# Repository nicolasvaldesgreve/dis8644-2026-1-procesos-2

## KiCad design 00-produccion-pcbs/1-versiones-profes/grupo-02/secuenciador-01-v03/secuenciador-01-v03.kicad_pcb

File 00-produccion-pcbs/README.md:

# produccion-pcbs

jornada maratónica sábado 06 junio 2026

equipo docente toma todos los proyectos de kicad entregados el día anterior, de proyecto-02, y con eso edita, revisa, y envía a producción.

hay 6 grupos de trabajo con una temática en particular, cada grupo realizó 2 esquemáticos con sus respectivas placas, en varias versiones que subieron a la carpeta 00-proyecto-02.

a continuación los apuntes de las distintas revisiones hechas de estos proyectos, para prepararlos para su producción física.

en este repo creamos 3 carpetas:

- 0-versiones-estudiantes: archivos de kicad con las versiones más recientes de proyectos de estudiantes
- 1-versiones-profes: archivos de kicad con las versiones revisadas y realizadas por equipo docentes
- 2-archivos-produccion: gerbers de producción, etiquetados como revA.

## grupo-01: piezos

- benjaminalvarez21
- Anaysval
- chknngttts
- ryukivol
- nicolasvaldesgreve

### g-01-pie-01-rev-a

- cambiamos tamaño r15
- cambiamos conector de entrada
- cambiamos nomenclatura de "100 u" a "100u"
- cambiamos huella de transistor Q1, porque era la equivocada

### g-01-pie-02-rev-a

- no fue enviado a producción porque no tenemos garantía de que funcionara según lo visto en protoboard.

## grupo-02: secuenciadores

- isidoraalvarez
- tomascatri
- dayanapanitrur
- Estrabismx
- angel-udp

### g-02-sec-01-rev-a

en esquemático:

- agregamos resistor de clock in a ground, para pulldown.
- agregamos resistor entre 4040 Q0 patita 9 y salida
- agregamos resistor a cada salida de jack switch.
- cambiamos huellas de transistores a versión inline_wide para que tengan más espacio
- agregados mounting hole faltantes

en pcb:

- actualizamos conectores jack a la huella de la biblioteca, para poder rutear bien los nuevos resistores y no perdernos.

### g-02-sec-02-rev-a

en esquemático:

- agregamos también resistores de protección en entradas y salidas.
- agregados mounting hole faltantes

en pcb:

- actualizamos conectores jack a la huella de la biblioteca, para poder rutear bien los nuevos resistores y no perdernos.

## grupo-03: osciladores 1

- vanessagarciaM
- antoloch
- ccarlabelenn
- arielorozco024
- Narelyriquelme

### g-03-osc-01-rev-a

- C1 estaba rotado, fue corregido.
- audio jack de entrada y salida estaban mal conectados
- condensador de salida fue cambiado por uno no polarizado

### g-03-osc-02-rev-a

- renombrar C3 a 4u7
- cambiado C1 por condensador polarizado
- 40106 fue usado como dos chips distintos, en vez de usar varios schmitt triggers desde un mismo chip, tuvimos que hacer esos cambios
- volvimos a rutear casi todo, ya que se bajó de 2 chips a 1

## grupo-04: osciladores 2

- antokiaraa
- santiagocifuvelez
- paulafuentesm
- kristelagj
- catalinaoyanedel
- yairaruiz

### g-04-osc-01-rev-a

- borramos amplificador para que esté en otro módulo
- agregamos resistencia de salida
- conectamos bien el jack de salida de audio que tenía problemas

### g-04-osc-02-rev-a

- borramos amplificador para que esté en otro módulo
- agregamos valor a diodo faltante
- corregimos símbolo de los potenciómetros
- agregamos resistencia de salida
- agregamos jack de salida de audio

## grupo-05: filtros

- antoniaamc
- Catabalboa
- sebastianguevaralarotta
- CatalinaJeria
- Luisaatoro9

### g-05-fil-01-rev-a

- error grave en la nomenclatura de los proyectos: el 01 en su README dicen que es el activo, pero en Kicad es el pasivo
- cambiamos C1 por condensador no polarizado
- conectamos patita del medio de potenciómetro
- confusión en los tamaños de los condensadores C4 y C5
- los tamaños de las pistas usados no fueron los indicados en clases ni en estandarización
- faltó el paso de agregar tierra a la placa, no está hecho

### g-05-fil-02-rev-a

- error grave en la nomenclatura de los proyectos: el 01 en su README dicen que es el activo, pero en Kicad es el pasivo
- no fue enviado a producción, ya que no funcionó en protoboard

## grupo-06: percusiones

- terroiblea
- martinaechavarria-stack
- Nicolas-Miranda1312
- paredesvania
- Coff4

### g-06-perc-01-rev-a

- agregamos jack de entrada de audio que reemplace la oscilación de entrada
- agregamos ground a los integrados que no están siendo usados

### g-06-perc-02-rev-a

- agregamos el detalle de las entradas de las compuertas lógicas no usadas, fueron conectadas a tierra, para definir sus estados
- C7 estaba en el esquemático pero no en la placa, tuvimos que agregarlo
- C4 le faltaba una conexión en la PCB, la agregamos

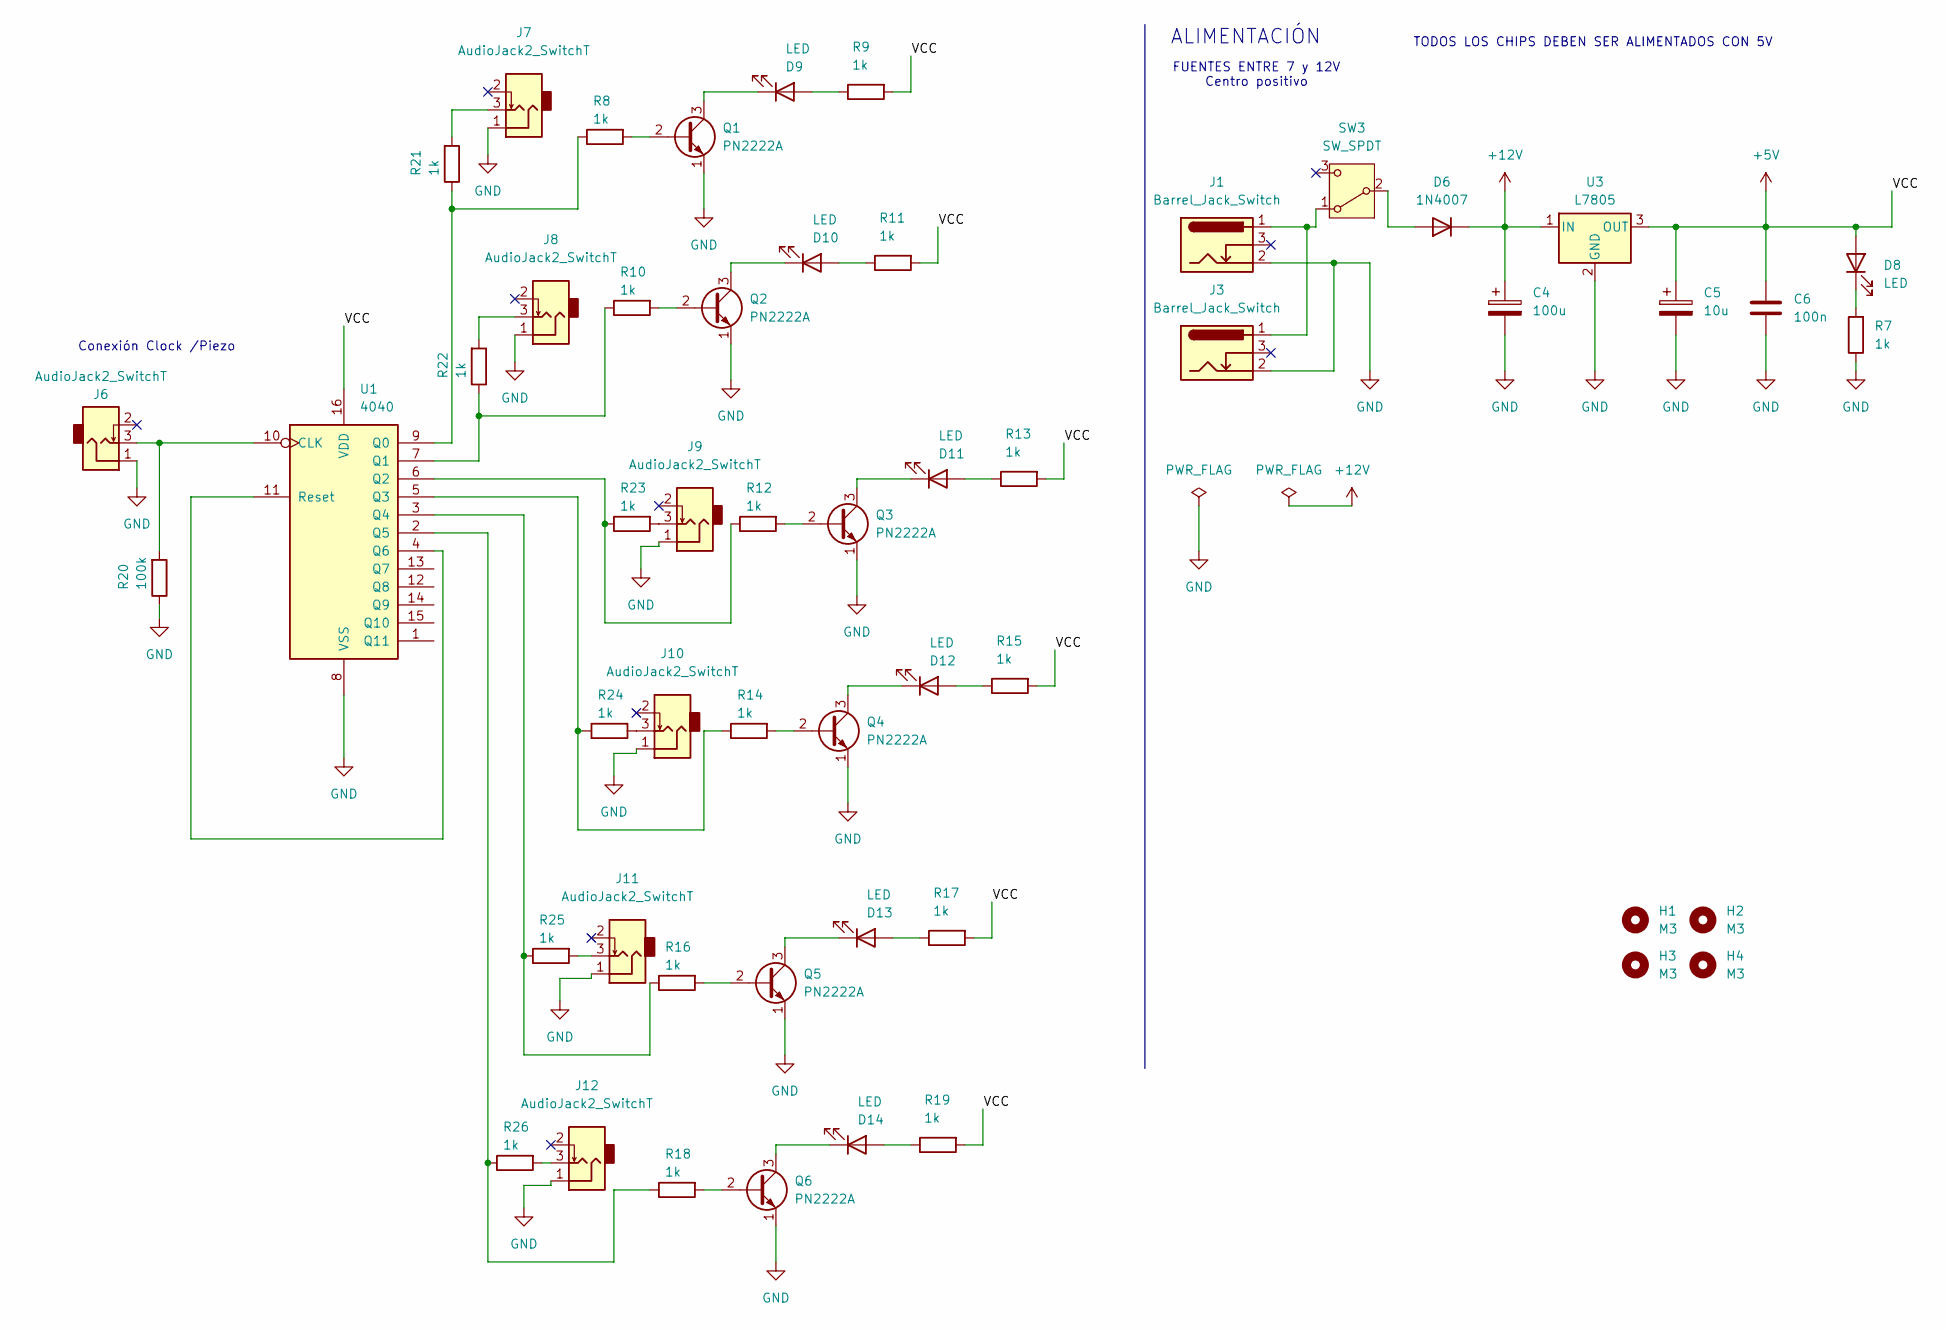
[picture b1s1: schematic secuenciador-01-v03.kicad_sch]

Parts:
C4: 100u; CP_Radial_D8.0mm_P3.80mm
C5: 10u; CP_Radial_D4.0mm_P2.00mm
C6: 100n; C_Disc_D5.0mm_W2.5mm_P2.50mm
D6: 1N4007; D_DO-41_SOD81_P10.16mm_Horizontal
D8, D9, D10, D11, D12, D13, D14: LED; LED_D5.0mm
H1, H2, H3, H4: M3; MountingHole_3.2mm_M3
J1, J3: Barrel_Jack_Switch; BarrelJack_Horizontal
J6, J7, J8, J9, J10, J11, J12: AudioJack2_SwitchT; PJ301M-12
Q1, Q2, Q3, Q4, Q5, Q6: PN2222A; TO-92_Inline_Wide
R7, R8, R9, R10, R11, R12, R13, R14, R15, R16, R17, R18, R19, R21, R22, R23, R24, R25, R26: 1k; R_Axial_DIN0207_L6.3mm_D2.5mm_P10.16mm_Horizontal
R20: 100k; R_Axial_DIN0207_L6.3mm_D2.5mm_P10.16mm_Horizontal
SW3: SW_SPDT; spdt_ssd12d00g3
U1: 4040; DIP-16_W7.62mm
U3: L7805; TO-220-3_Horizontal_TabDown

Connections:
+5V: C5.1, C6.1, D8.2 (A), R9.2, R11.2, R13.2, R15.2, R17.2, R19.2, U1.16 (VDD), U3.3 (OUT)
+12V: C4.1, D6.1 (K), U3.1 (IN)
GND: C4.2, C5.2, C6.2, J1.2, J3.2, J6.1, J7.1, J8.1, J9.1, J10.1, J11.1, J12.1, Q1.1 (E), Q2.1 (E), Q3.1 (E), Q4.1 (E), Q5.1 (E), Q6.1 (E), R7.1, R20.1, U1.8 (VSS), U3.2 (GND)
unnamed: D6.2 (A), SW3.2 (B)
unnamed: D8.1 (K), R7.2
unnamed: D9.2 (A), R9.1
unnamed: D9.1 (K), Q1.3 (C)
unnamed: D10.2 (A), R11.1
unnamed: D10.1 (K), Q2.3 (C)
unnamed: D11.2 (A), R13.1
unnamed: D11.1 (K), Q3.3 (C)
unnamed: D12.2 (A), R15.1
unnamed: D12.1 (K), Q4.3 (C)
unnamed: D13.2 (A), R17.1
unnamed: D13.1 (K), Q5.3 (C)
unnamed: D14.2 (A), R19.1
unnamed: D14.1 (K), Q6.3 (C)
unnamed: J7.3, R21.2
unnamed: J8.3, R22.2
unnamed: J9.3, R23.2
unnamed: J10.3, R24.2
unnamed: J11.3, R25.2
unnamed: J12.3, R26.2
unnamed: Q1.2 (B), R8.2
unnamed: Q2.2 (B), R10.2
unnamed: Q3.2 (B), R12.2
unnamed: Q4.2 (B), R14.2
unnamed: Q5.2 (B), R16.2
unnamed: Q6.2 (B), R18.2
unnamed: J1.1, J3.1, SW3.1 (A)
unnamed: J6.3, R20.2, U1.10 (CLK)
unnamed: R8.1, R21.1, U1.9 (Q0)
unnamed: R10.1, R22.1, U1.7 (Q1)
unnamed: R12.1, R23.1, U1.6 (Q2)
unnamed: R14.1, R24.1, U1.5 (Q3)
unnamed: R16.1, R25.1, U1.3 (Q4)
unnamed: R18.1, R26.1, U1.2 (Q5)
unnamed: U1.4 (Q6), U1.11 (Reset)

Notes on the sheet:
Conexión Clock /Piezo
ALIMENTACIÓN
FUENTES ENTRE 7 y 12V Centro positivo
TODOS LOS CHIPS DEBEN SER ALIMENTADOS CON 5V

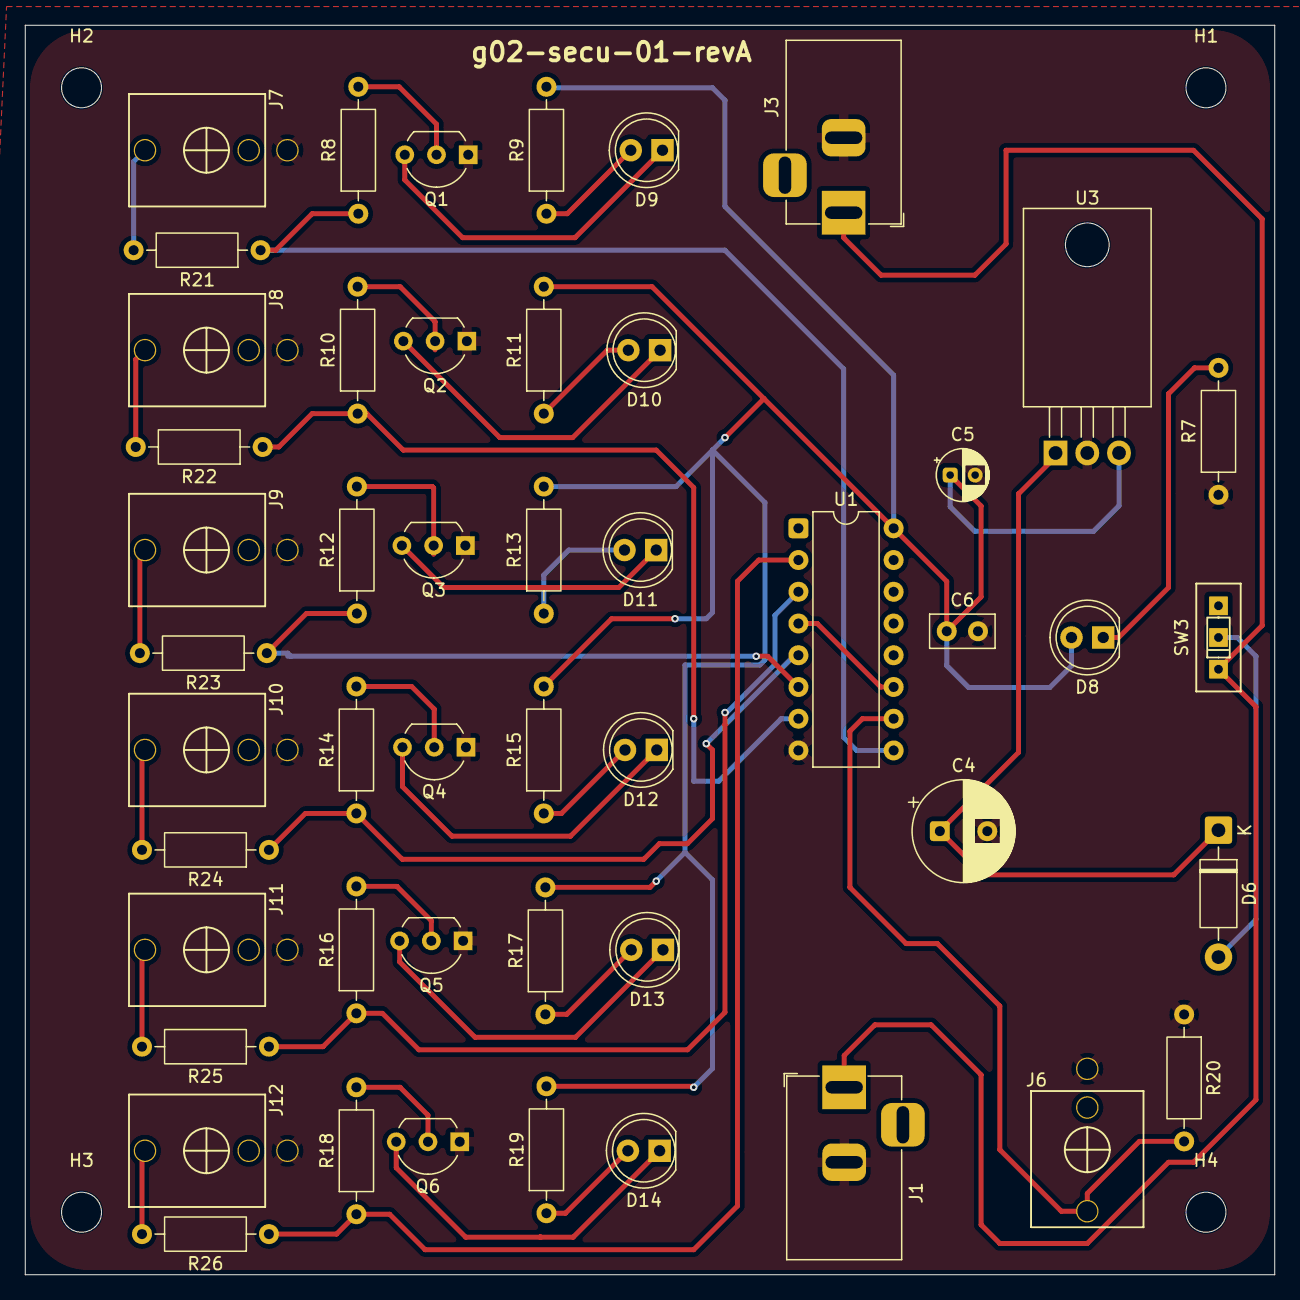
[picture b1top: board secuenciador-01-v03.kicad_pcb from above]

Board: 2 copper layers, 100.0 x 100.0 mm, 53 parts (0 on the bottom side), 38 nets.

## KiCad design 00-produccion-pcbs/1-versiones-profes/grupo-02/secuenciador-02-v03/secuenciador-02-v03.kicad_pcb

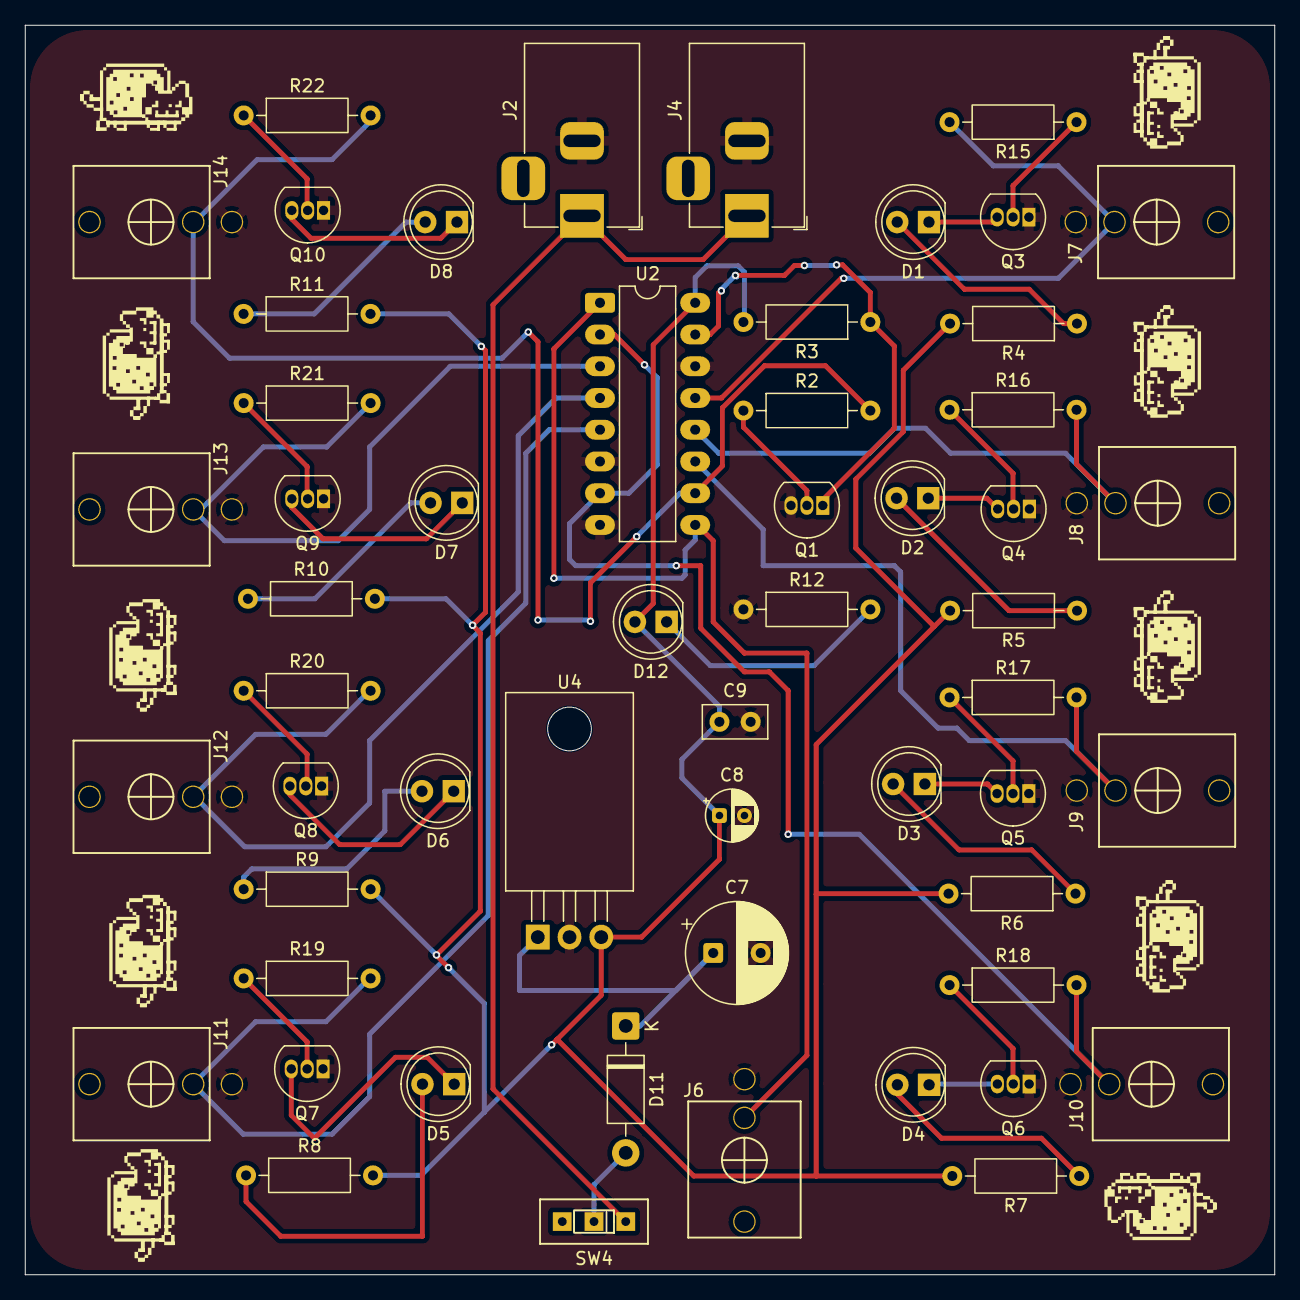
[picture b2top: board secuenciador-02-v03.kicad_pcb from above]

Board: 2 copper layers, 100.0 x 100.0 mm, 55 parts (0 on the bottom side), 41 nets.

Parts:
C7: 100u; CP_Radial_D8.0mm_P3.80mm
C8: 10u; CP_Radial_D4.0mm_P2.00mm
C9: 100n; C_Disc_D5.0mm_W2.5mm_P2.50mm
D1, D2, D3, D4, D5, D6, D7, D8, D12: LED; LED_D5.0mm
D11: 1N4007; D_DO-41_SOD81_P10.16mm_Horizontal
J2, J4: Barrel_Jack_Switch; BarrelJack_Horizontal
J6, J7, J8, J9, J10, J11, J12, J13, J14: AudioJack2_SwitchT; PJ301M-12
Q1: BC548; TO-92_Inline
Q3, Q4, Q5, Q6, Q7, Q8, Q9, Q10: PN2222A; TO-92_Inline
R2: 10k; R_Axial_DIN0207_L6.3mm_D2.5mm_P10.16mm_Horizontal
R3, R12, R15, R16, R17, R18, R19, R20, R21, R22: 1k; R_Axial_DIN0207_L6.3mm_D2.5mm_P10.16mm_Horizontal
R4, R5, R6, R7, R8, R9, R10, R11: 220; R_Axial_DIN0207_L6.3mm_D2.5mm_P10.16mm_Horizontal
SW4: SW_SPDT; spdt_ssd12d00g3
U2: 4015; DIP-16_W7.62mm_LongPads
U4: L7805; TO-220-3_Horizontal_TabDown

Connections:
+5V: C8.1, C9.1, D12.2 (A), R3.2, R4.2, R5.2, R6.2, R7.2, R8.2, R9.2, R10.2, R11.2, U2.16 (Vdd), U4.3 (OUT)
+12V: C7.1, D11.1 (K), U4.1 (IN)
GND: C7.2, C8.2, C9.2, J2.2, J4.2, J6.1, J7.1, J8.1, J9.1, J10.1, J11.1, J12.1, J13.1, J14.1, Q1.3 (E), Q3.1 (E), Q4.1 (E), Q5.1 (E), Q6.1 (E), Q7.1 (E), Q8.1 (E), Q9.1 (E), Q10.1 (E), R12.1, U2.6 (MR), U2.8 (Vss), U2.14 (MR), U4.2 (GND)
unnamed: D1.2 (A), R4.1
unnamed: D1.1 (K), Q3.3 (C)
unnamed: D2.2 (A), R5.1
unnamed: D2.1 (K), Q4.3 (C)
unnamed: D3.2 (A), R6.1
unnamed: D3.1 (K), Q5.3 (C)
unnamed: D4.2 (A), R7.1
unnamed: D4.1 (K), Q6.3 (C)
unnamed: D5.2 (A), R8.1
unnamed: D5.1 (K), Q7.3 (C)
unnamed: D6.2 (A), R9.1
unnamed: D6.1 (K), Q8.3 (C)
unnamed: D7.2 (A), R10.1
unnamed: D7.1 (K), Q9.3 (C)
unnamed: D8.2 (A), R11.1
unnamed: D8.1 (K), Q10.3 (C)
unnamed: D11.2 (A), SW4.2 (B)
unnamed: D12.1 (K), R12.2
unnamed: Q1.2 (B), R2.1
unnamed: Q1.1 (C), R3.1, U2.15 (D)
unnamed: Q3.2 (B), R15.1
unnamed: Q4.2 (B), R16.1
unnamed: Q5.2 (B), R17.1
unnamed: Q6.2 (B), R18.1
unnamed: Q7.2 (B), R19.1
unnamed: Q8.2 (B), R20.1
unnamed: Q9.2 (B), R21.1
unnamed: Q10.2 (B), R22.1
unnamed: J2.1, J4.1, SW4.1 (A)
unnamed: J6.3, U2.1 (CP), U2.9 (CP)
unnamed: J10.3, R18.2, U2.2 (Q4), U2.7 (D)
unnamed: J11.3, R19.2, U2.5 (Q1)
unnamed: J12.3, R20.2, U2.4 (Q2)
unnamed: J13.3, R21.2, U2.3 (Q3)
unnamed: J14.3, R2.2, R22.2, U2.10 (Q4)
unnamed: J7.3, R15.2, U2.13 (Q1)
unnamed: J8.3, R16.2, U2.12 (Q2)
unnamed: J9.3, R17.2, U2.11 (Q3)

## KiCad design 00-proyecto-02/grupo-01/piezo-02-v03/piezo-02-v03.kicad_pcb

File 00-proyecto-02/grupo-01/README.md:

# proyecto-02

## Grupo

Número de grupo: 01

Tema del grupo: Piezo

Integrantes:

- Benjamín Alonso Álvarez Pavez / [benjaminalvarez21](<https://github.com/disenoUDP/dis8644-2026-1-procesos-2/tree/main/03-benjaminalvarez21>)
- Anays Valentina Cornejo Candia / [Anaysval](<https://github.com/disenoUDP/dis8644-2026-1-procesos-2/tree/main/09-Anaysval>)
- Bruno Ferrari Meyer / [chknngttts](<https://github.com/disenoUDP/dis8644-2026-1-procesos-2/tree/main/11-chknngttts>)
- Lucas Ignacio Ortiz Aguirre / [ryukivol](<https://github.com/disenoUDP/dis8644-2026-1-procesos-2/tree/main/21-ryukivol>)
- Nicolás Elías Valdés Greve / [nicolasvaldesgreve](<https://github.com/disenoUDP/dis8644-2026-1-procesos-2/tree/main/31-nicolasvaldesgreve>)

## Circuito 1

maincra

### Descripción general/conceptual 1

Este módulo te permite interactuar con el sintetizador mediante vibraciones en el piezo, tales como golpes en la misma superficie en la que se encuentra el componente o utilizándolo en nuestro cuerpo y causar vibraciones con nuestra garganta. Estas vibraciones serás captadas por el piezo, lo cual lo tomará como señal para avanzar en el secuenciador.

### Descripción de funcionamiento 1

El circuito se conforma de 7 partes:
  - Piezoeléctrico
  - Pre-Amp (TL072)
  - Inversor de señal (2N2222)
  - Regulador de voltaje (L7805CV)
  - Filtro Low-pass
  - Clock (NE555P)
  - Secuenciador (CD4017)

Como estándar en el trabajo todos tenemos que alimentar nuestro circuito con 5V. Para esto usamos el L7805CV

El piezo tiene 3 estados al recibir señal.

Para que el Pre-Amp pueda recibir la señal correctamente se necesita crear un voltaje medio entre VCC y GND. Para esto se usan 2 Resistencias del mismo valor, que dividen el voltaje a la mitad **``5V ---> 2.5V``**, esto permite que capte la señal completa y funcione correctamente. El Pre-Amp en nuestro caso también funciona para aumentar la sensibilidad del piezo, normalmente este solo detecta las señales directas al disco cerámico del piezo, pero con el Pre-Amp logramos que detecte señales a varios centímetros de este. 

Para afinar la señal que recibe el inversor, colocamos un filtro low-pass, esto permite que solo corriente bajo los 500hz *aprox.* avancen en el circuito. Esta señal entra al transistor (2N2222) que invierte la señal que recibe, puesto que el Clock (NE555P) busca recibir señales negativas en su Trigger [pin 2] para funcionar. El Clock en modo monoestable se conecta con el pin 14 del secuenciador (CD4017) para que señale cuando se avanza en los steps. 

### Descubrimientos

- Modificando los valores de las resistencias, se logra amplificar la sensibilidad del piezo (gracias misaaaaaa).
- Tener protoboard con los orificios **no** suelto es vital para que el circuito sea estable y se pueda mover.
- Que ciertos amplificadores tienen usos específicos, como el LM386 que es óptimo para parlantes, pero no piezos.
- Se pueden sustituir componentes con valores diferentes **``2.2k Ω ---> 47 Ω``**

### Esquemático 

### PCB 1

### Documentación audiovisual funcionamiento protoboard 1

[video-piezo-01](https://youtu.be/JZCzPmO_yxs)

### BOM

| Componente | Cantidad | Valor unitario | Link |
| --- | --- | --- | --- |
| Chip NE555P | 1 | $490 | <https://www.victronics.cl/circuitos-integrados/lm555cngeneralpurposebipolartimerdip8/> |
| Chip TL072CP | 1 | $990 | <https://www.victronics.cl/circuitos-integrados/tl072cpdualjfetlowpoweropamplifierdip8/> |
| Chip CD4017 | 1 | $890 | <https://www.mechatronicstore.cl/circuito-integrado-4017-contador/?srsltid=AfmBOopG29clQvJ0CqcNNp17wxEDjZ1w8dAWqRPMAcTqycciqYjHE40h>
| Regulador L7805CV | 1 | $350 | <https://www.victronics.cl/reguladores/reguladorvoltl7805cv5v-15ato220/> |
| Diodo 1N4007 | 1 | $200 | <https://www.mechatronicstore.cl/diodo-rectificador-in4007-1n4007-4007/> |
| Diodo BAT85 | 2 | $586 | <https://cl.rsdelivers.com/product/nexperia/bat85113/nexperia-diodo-bat85113-diodo-schottky-200-ma-30-v/0300978> |
| Transistor 2N2222 | 1 | $200 | <https://www.mechatronicstore.cl/transistor-2n2222/> |
| Potenciómetro B10K | 1 | $495 | <https://altronics.cl/potenciometro-lineal-10k-b10k> |
| Potenciómetro B500K | 1 | $495 | <https://altronics.cl/potenciometro-lineal-500k-b500k?search=b500k> |
| LED 3mm | 5 | $100 | <https://www.mechatronicstore.cl/led-3mm-5mm/> |
| Resistencia 47 Ω | 1 | $90 | <https://www.electroardu.cl/resistencias-1k-ohm?srsltid=AfmBOor81HKrzfoOTnLK3FU6ObPuf1EPUVMS0naCwqMNIzGt8LYDiUYt> |
| Resistencia 100 Ω | 1 | $90 | <https://www.electroardu.cl/resistencias-1k-ohm?srsltid=AfmBOor81HKrzfoOTnLK3FU6ObPuf1EPUVMS0naCwqMNIzGt8LYDiUYt> |
| Resistencia 220 Ω | 1 | $90 | <https://www.electroardu.cl/resistencias-1k-ohm?srsltid=AfmBOor81HKrzfoOTnLK3FU6ObPuf1EPUVMS0naCwqMNIzGt8LYDiUYt> |
| Resistencia 1 KΩ | 8 | $90 | <https://www.electroardu.cl/resistencias-1k-ohm?srsltid=AfmBOor81HKrzfoOTnLK3FU6ObPuf1EPUVMS0naCwqMNIzGt8LYDiUYt> |
| Resistencia 10 KΩ | 4 | $90 | <https://www.electroardu.cl/resistencias-1k-ohm?srsltid=AfmBOor81HKrzfoOTnLK3FU6ObPuf1EPUVMS0naCwqMNIzGt8LYDiUYt> |
| Resistencia 100 KΩ | 5 | $90 | <https://www.electroardu.cl/resistencias-1k-ohm?srsltid=AfmBOor81HKrzfoOTnLK3FU6ObPuf1EPUVMS0naCwqMNIzGt8LYDiUYt> |
| Condensador cerámico 4.7 nF | 1 | $100 | <https://www.mechatronicstore.cl/condensadores-ceramicos-distintos-valores/> |
| Condensador cerámico 10 nF | 1 | $100 | <https://www.mechatronicstore.cl/condensadores-ceramicos-distintos-valores/> |
| Condensador cerámico 100 nF | 4 | $100 | <https://www.mechatronicstore.cl/condensadores-ceramicos-distintos-valores/> |
| Condensador polarizado 10 µF | 2 | $100 | <https://www.mechatronicstore.cl/condensador-capacitorio-de-electrolitico-por-unidad-varios-valores/> |
| Condensador polarizado 100 µF | 3 | $100 | <https://www.mechatronicstore.cl/condensador-capacitorio-de-electrolitico-por-unidad-varios-valores/> | 
| Cables dupont 40 uni. | 1 | $2.990 | <https://mcielectronics.cl/shop/product/cable-dupont-macho-macho-20cm-pack-40-unidades-2/> |
| Cables caimán | 2 | $1.990 | <https://www.mechatronicstore.cl/cable-conector-cocodrilo-o-caiman-5-unidades/> |
| Batería 9V recargable | 1 | $7.990 | <https://www.sodimac.cl/sodimac-cl/articulo/110251085/bateria-recargable-9v/110251089> |
| Conector batería | 1 | $1.990 | <https://mcielectronics.cl/shop/product/conector-para-baterias-de-9v-9800/?srsltid=AfmBOorf4iqHmZZbBCSLCPoI-UFTBMuBMtXEwLw-ia48KteW5jir8sIx> |
| Piezo | 1 | $990 | <https://www.mechatronicstore.cl/sensor-piezoelectrico-27mm-con-cable/> |
| Interruptor Switch | 1 | $570 | <https://www.katode.cl/switches/1339-interruptor-switch-2-pines-on-off-corto.html?srsltid=AfmBOorJlIeUySzAORFwXSattHKE4BKH2LmhhXZS_8fZ4MW-G6kwnxqA> |

## Circuito 2

Budumtz

### Descripción general/conceptual 2

Este módulo, al igual que el anterior, permite que uno pueda interactuar con el sintetizador al que esté conectado el piezo, pero en este caso se necesita contacto directo al componente lo cual permitirá que lo que esté conectado a este se active.

### Descripción de funcionamiento 2

El circuito se conforma por 4 partes:

+ Piezoeléctrico
+ High pass filter
+ Op-Amp (LM324)
+ Inversor de señal (2N2222)
+ Regulador de voltaje (L7805CV)

Este circuito emplea el funcionamiento de *activador* es decir, envía señal a un módulo siguiente, el cual para verificar su funcionamiento se utiliza un led o se puede conectar a una salida de audio utilizando un Amp y parlante. 

El chip LM324 se utiliza como DC offset, regulando el voltaje bajando a la mitad **``9V ---> 4.5V``**. Además, cuenta con una salida de audio [pin 7] que utilizamos como salida para el siguiente módulo. De esta manera al interactuar con el piezo la señal se ve distorsionada por un breve periodo de tiempo ya que la señal que emite el circuito es constante.

En cuanto a los reguladores de voltaje, ya que nuestro chip LM324 cuenta con uno decidimos crear dos versiones, una con el estándar dado para la sección y uno con el integrado en el circuito.

Por otro lado, tuvimos un problema relacionado con la PCB, al ejecutar DRC da error: conexión de alivio térmico a zona incompleta al [pin 11] con el GND, problema que intentamos solucionar, pero no hubo éxito.

Archivo piezo-02-v03: Con regulador estándar.

Archivo piezo-02-v04: Solo regulador integrado.

### Esquemático 2

### PCB 2

### Documentación audiovisual funcionamiento protoboard 2

[video-piezo-02](https://youtu.be/MbAfNLuIrsg)

### BOM

| Componente | Cantidad | Valor unitario | Link |
| --- | --- | --- | --- |
| Chip LM324 | 1 | $590 | <https://www.mechatronicstore.cl/amplificador-operacional-lm324/?srsltid=AfmBOopyXPPvl24e9VRGUKZwKS9_gIp9S3hdacmTDOWF4O2ur2TF77QZ> |
| Potenciómetro B500K | 1 | $495 | <https://altronics.cl/potenciometro-lineal-500k-b500k?search=b500k> |
| LED 3mm | 1 | $100 | <https://www.mechatronicstore.cl/led-3mm-5mm/> |
| Transistor 2N2222 | 1 | $200 | <https://www.mechatronicstore.cl/transistor-2n2222/> |
| Resistencia 1 KΩ | 3| $90 | <https://www.electroardu.cl/resistencias-1k-ohm?srsltid=AfmBOor81HKrzfoOTnLK3FU6ObPuf1EPUVMS0naCwqMNIzGt8LYDiUYt> |
| Resistencia 10 KΩ | 1 | $90 | <https://www.electroardu.cl/resistencias-1k-ohm?srsltid=AfmBOor81HKrzfoOTnLK3FU6ObPuf1EPUVMS0naCwqMNIzGt8LYDiUYt> |
| Resistencia 22K KΩ | 1 | $90 | <https://www.electroardu.cl/resistencias-1k-ohm?srsltid=AfmBOor81HKrzfoOTnLK3FU6ObPuf1EPUVMS0naCwqMNIzGt8LYDiUYt> |
| Resistencia 100 KΩ | 3 | $90 | <https://www.electroardu.cl/resistencias-1k-ohm?srsltid=AfmBOor81HKrzfoOTnLK3FU6ObPuf1EPUVMS0naCwqMNIzGt8LYDiUYt> |
| Resistencia 1 MΩ | 3 | $90 | <https://www.electroardu.cl/resistencias-1k-ohm?srsltid=AfmBOor81HKrzfoOTnLK3FU6ObPuf1EPUVMS0naCwqMNIzGt8LYDiUYt> |
| Condensador cerámico 4.7 nF | 1 | $100 | <https://www.mechatronicstore.cl/condensadores-ceramicos-distintos-valores/> |
| Condensador cerámico 100 nF | 2 | $100 | <https://www.mechatronicstore.cl/condensadores-ceramicos-distintos-valores/> |
| Condensador polarizado 10 µF | 2 | $100 | <https://www.mechatronicstore.cl/condensador-capacitorio-de-electrolitico-por-unidad-varios-valores/>|
| Condensador polarizado 100 µF | 2 | $100 | <https://www.mechatronicstore.cl/condensador-capacitorio-de-electrolitico-por-unidad-varios-valores/> | 
| Cables dupont 40 uni. | 1 | $2.990 | <https://mcielectronics.cl/shop/product/cable-dupont-macho-macho-20cm-pack-40-unidades-2/> |
| Cables caimán | 2 | $1.990 | <https://www.mechatronicstore.cl/cable-conector-cocodrilo-o-caiman-5-unidades/> |
| Batería 9V recargable | 1 | $7.990 | <https://www.sodimac.cl/sodimac-cl/articulo/110251085/bateria-recargable-9v/110251089> |
| Conector batería | 1 | $1.990 | <https://mcielectronics.cl/shop/product/conector-para-baterias-de-9v-9800/?srsltid=AfmBOorf4iqHmZZbBCSLCPoI-UFTBMuBMtXEwLw-ia48KteW5jir8sIx> |
| Piezo | 1 | $990 | <https://www.mechatronicstore.cl/sensor-piezoelectrico-27mm-con-cable/> |
| Interruptor Switch | 1 | $570 | <https://www.katode.cl/switches/1339-interruptor-switch-2-pines-on-off-corto.html?srsltid=AfmBOorJlIeUySzAORFwXSattHKE4BKH2LmhhXZS_8fZ4MW-G6kwnxqA> |

## Otros circuitos

En el piezo 01 usamos el HiFi Pre-Amp Circuit de [jevron1984](https://electronics.stackexchange.com/questions/348898/need-some-help-building-a-tl072-preamp-circuit).

No era compatible con el circuito, después armamos un circuito propio utilizando el 2N2222, pero tampoco funcionó, por lo que lo sustituimos por el Pre-Amp de [PimPom](https://www.diyaudio.com/community/threads/tl072-as-mike-input-preamp.317907/).

En el piezo 02 armamos un Amp con el LM386, siguiendo el mismo esquemático que se nos entregó por misaaaaaa en el proyecto-01.

## Colaboración con otros grupos

### ¿Cómo ayudé a otro grupo?

+ Ayudamos al grupo 03 (osciladores 1) prestándoles dos potenciómetros B100K.
+ Ayudamos al grupo 03 (osciladores 1) con el comando para añadir imágenes en el README.md.
+ Ayudamos al grupo 03 (osciladores 1) con la gráfica de la PCB.
+ Ayudamos al grupo 06 (percutores) prestándoles la batería.
+ Ayudamos al grupo 06 (percutores) con las pistas en su PCB.

### ¿Cómo me ayudó otro grupo?

+ Santiago Cifuentes del grupo 04 (osciladores 2) nos ayudó con la compra de componentes y apoyo emocional de manera constante tanto dentro como fuera de clases.
+ Yaira Ruiz nos ayudó a agregar las carpetas que contienen las huellas del curso.
+ Martína Echavarria del grupo 06 (percutores) nos ayudó cargando la batería.

## Bibliografía

+ Colectivo 22bits. (2020, 8 1). Hybrida. GitHub. <https://github.com/22bits/Matrinicas/blob/master/Hybrida/HYBRIDA_Esquematico.pdf>

+ DigiKey. (n.d.). Voltage Divider Conversion Calculator. DigiKey. <https://www.digikey.com/en/resources/conversion-calculators/conversion-calculator-voltage-divider>

+ jevron1984. (2018, January 8). Need some help building a TL072 preamp circuit. Electronics Stack Exchange. <https://electronics.stackexchange.com/questions/348898/need-some-help-building-a-tl072-preamp-circuit>

+ misaaaaaa. (n.d.). transistoresDeclaman. GitHub. <https://github.com/misaaaaaa/transistoresDeclaman/blob/main/sch.pdf>

+ Pimpom. (2018, 1 25). TL072 as mike input preamp. diyAudio. <https://www.diyaudio.com/community/threads/tl072-as-mike-input-preamp.317907/>

+ kickstomp. (2021, 3 27). 06 Piezo Trigger. arduinokickstompdrum. <https://arduinokickstompdrum.wordpress.com/2021/05/27/06-piezo-trigger/>

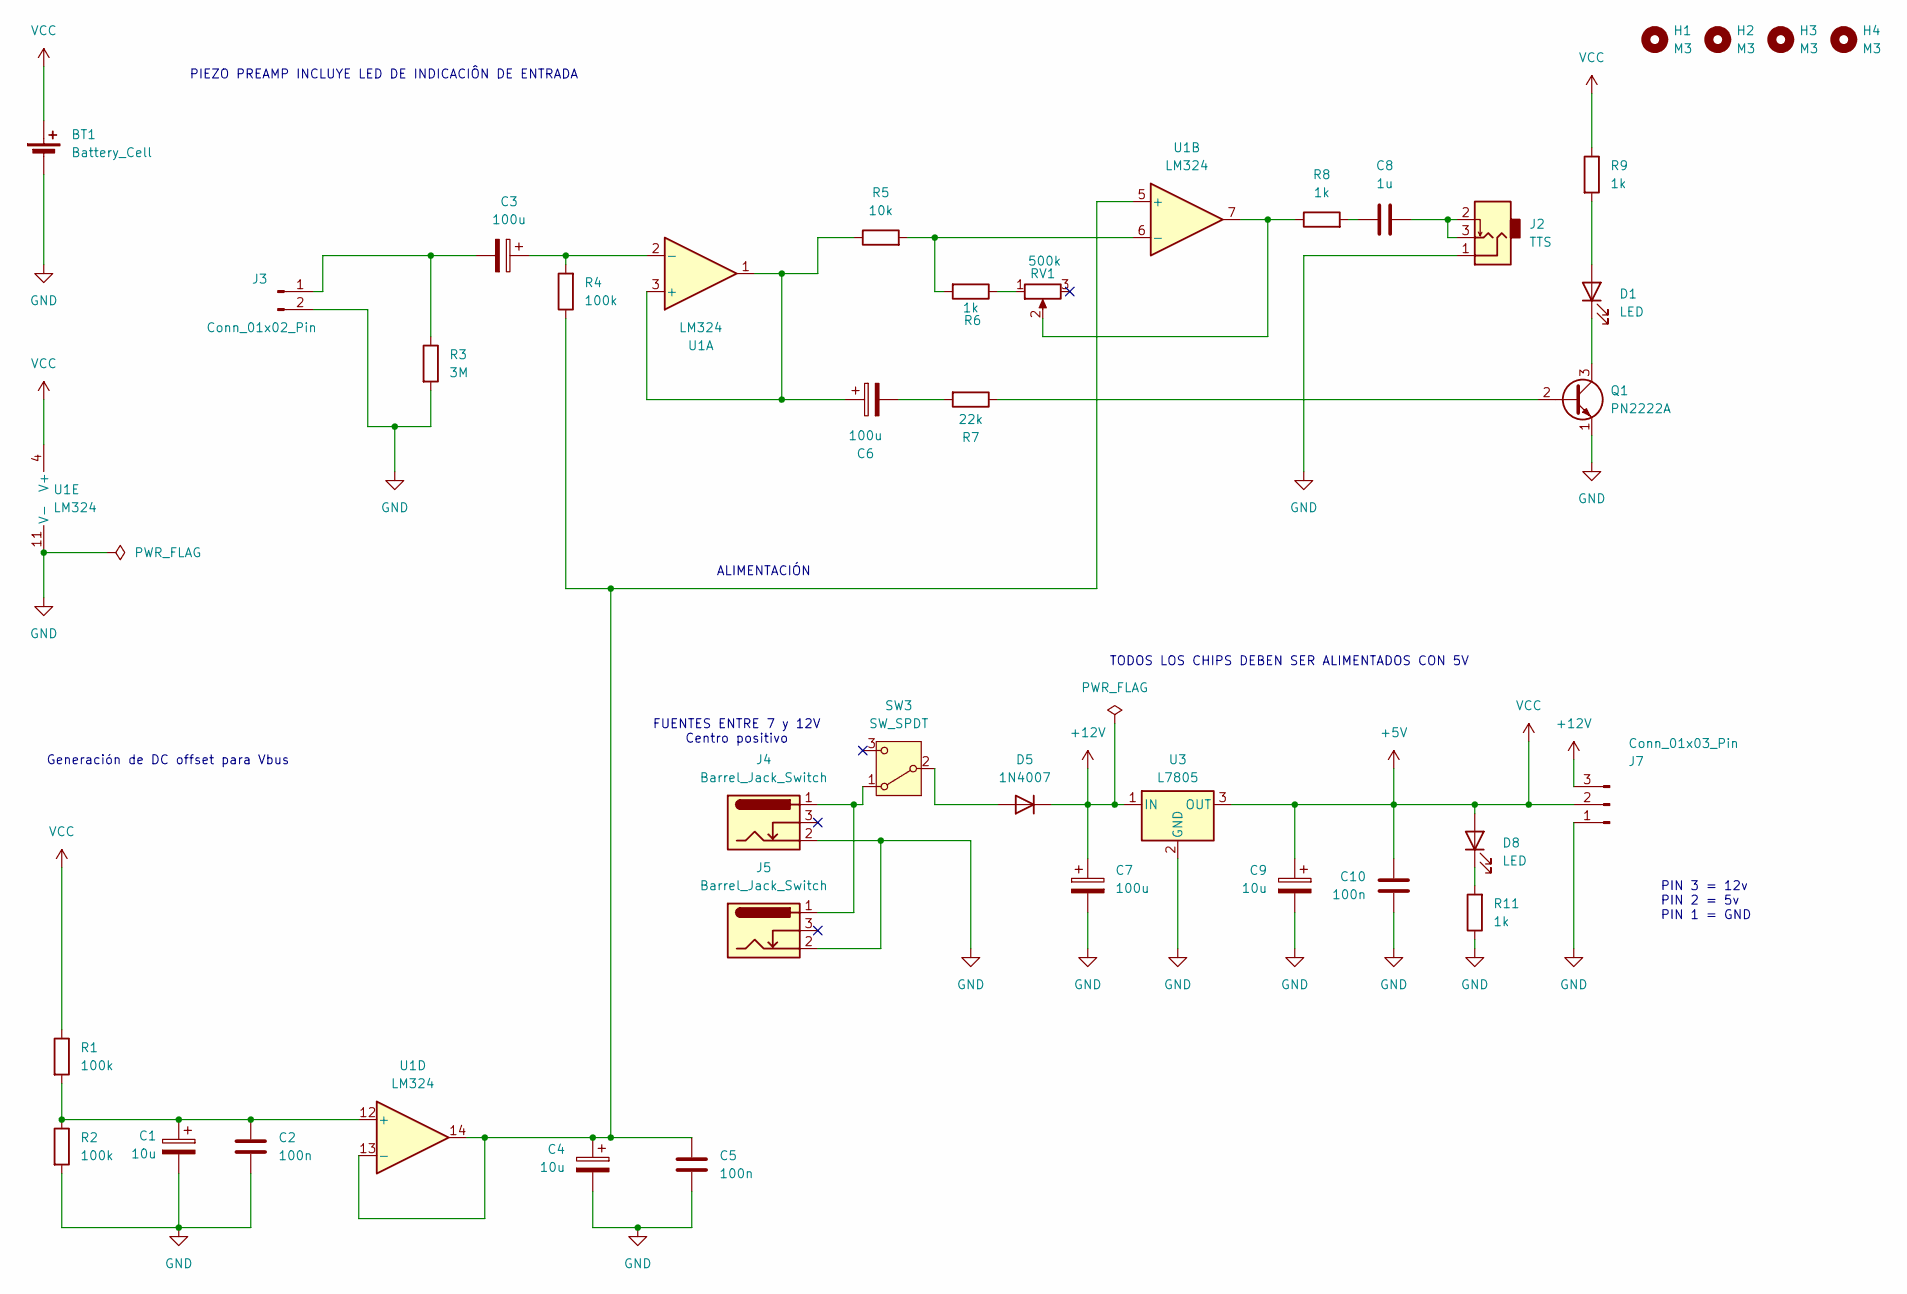
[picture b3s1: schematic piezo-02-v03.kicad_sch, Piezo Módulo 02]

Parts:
BT1: Battery_Cell; TerminalBlock_MaiXu_MX126-5.0-02P_1x02_P5.00mm
C1, C4, C9: 10u; CP_Radial_D4.0mm_P2.00mm
C2, C5, C10: 100n; C_Disc_D5.0mm_W2.5mm_P2.50mm
C3, C6, C7: 100u; CP_Radial_D8.0mm_P3.80mm
C8: 1u; C_Disc_D5.0mm_W2.5mm_P5.00mm
D1, D8: LED; LED_D5.0mm
D5: 1N4007; D_DO-41_SOD81_P10.16mm_Horizontal
H1, H2, H3, H4: M3; MountingHole_3.2mm_M3
J2: TTS; PJ301M-12
J3: Conn_01x02_Pin; PinSocket_1x02_P2.54mm_Vertical
J4, J5: Barrel_Jack_Switch; BarrelJack_Horizontal
J7: Conn_01x03_Pin; PinSocket_1x03_P2.54mm_Vertical
Q1: PN2222A; TO-92_Inline
R1, R2, R4: 100k; R_Axial_DIN0207_L6.3mm_D2.5mm_P10.16mm_Horizontal
R3: 3M; R_Axial_DIN0207_L6.3mm_D2.5mm_P10.16mm_Horizontal
R5: 10k; R_Axial_DIN0207_L6.3mm_D2.5mm_P10.16mm_Horizontal
R6, R8, R9, R11: 1k; R_Axial_DIN0207_L6.3mm_D2.5mm_P10.16mm_Horizontal
R7: 22k; R_Axial_DIN0207_L6.3mm_D2.5mm_P10.16mm_Horizontal
RV1: 500k; Potentiometer_Alps_RK163_Single_Horizontal
SW3: SW_SPDT; spdt_ssd12d00g3
U1: LM324; DIP-14_W7.62mm_LongPads
U3: L7805; TO-220-3_Vertical

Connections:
+5V: BT1.1 (+), C9.1, C10.1, D8.2 (A), J7.2, R1.1, R9.1, U1.4 (V+), U3.3 (OUT)
+12V: C7.1, D5.1 (K), J7.3, U3.1 (IN)
GND: BT1.2 (-), C1.2, C2.2, C4.2, C5.2, C7.2, C9.2, C10.2, J2.1, J3.2, J4.2, J5.2, J7.1, Q1.1 (E), R2.2, R3.2, R11.1, U1.11 (V-), U3.2 (GND)
unnamed: C6.2, R7.2
unnamed: C8.1, R8.2
unnamed: C8.2, J2.2, J2.3
unnamed: D1.2 (A), R9.2
unnamed: D1.1 (K), Q1.3 (C)
unnamed: D5.2 (A), SW3.2 (B)
unnamed: D8.1 (K), R11.2
unnamed: C3.2, J3.1, R3.1
unnamed: Q1.2 (B), R7.1
unnamed: R6.1, RV1.1
unnamed: R8.1, RV1.2, U1.7
unnamed: J4.1, J5.1, SW3.1 (A)
unnamed: C6.1, R5.1, U1.1, U1.3 (+)
unnamed: C3.1, R4.2, U1.2 (-)
unnamed: C4.1, C5.1, R4.1, U1.5 (+), U1.13 (-), U1.14
unnamed: R5.2, R6.2, U1.6 (-)
unnamed: C1.1, C2.1, R1.2, R2.1, U1.12 (+)

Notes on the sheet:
TODOS LOS CHIPS DEBEN SER ALIMENTADOS CON 5V
PIEZO PREAMP INCLUYE LED DE INDICACIÔN DE ENTRADA
FUENTES ENTRE 7 y 12V Centro positivo
ALIMENTACIÓN
PIN 3 = 12v PIN 2 = 5v PIN 1 = GND
Generación de DC offset para Vbus

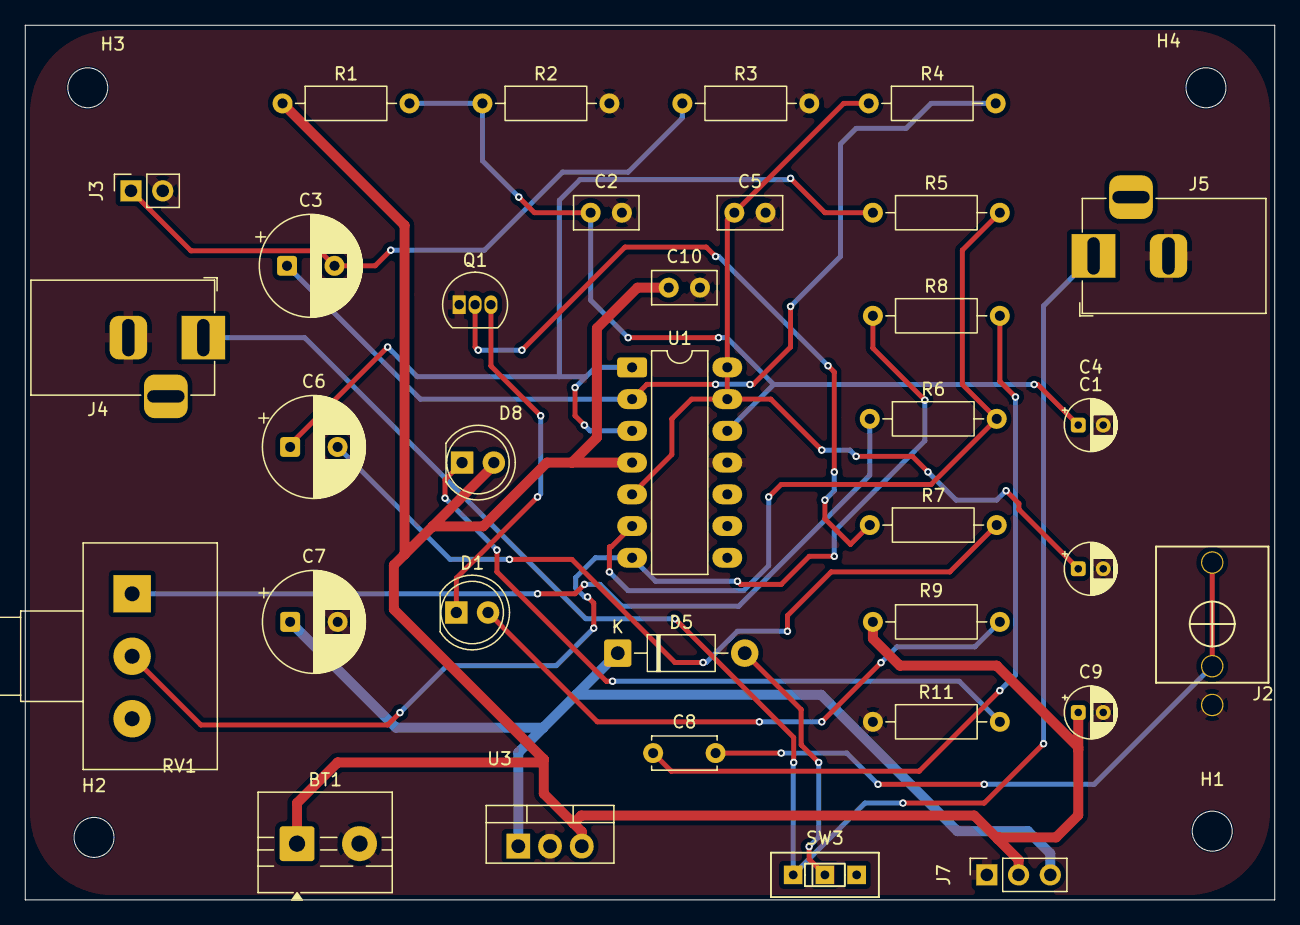
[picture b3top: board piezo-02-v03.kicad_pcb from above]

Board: 2 copper layers, 100.0 x 70.0 mm, 38 parts (0 on the bottom side), 20 nets.
